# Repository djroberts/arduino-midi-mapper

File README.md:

# arduino-midi-mapper
Midi mapper using an arduino nano.

The main object is to create a device between a Gig Rig and a Digitech Whammy DT which maps program changes from the Gig Rig to the fixed patches on the DT. 

Requires the Arduino Midi Library
http://playground.arduino.cc/Main/MIDILibrary

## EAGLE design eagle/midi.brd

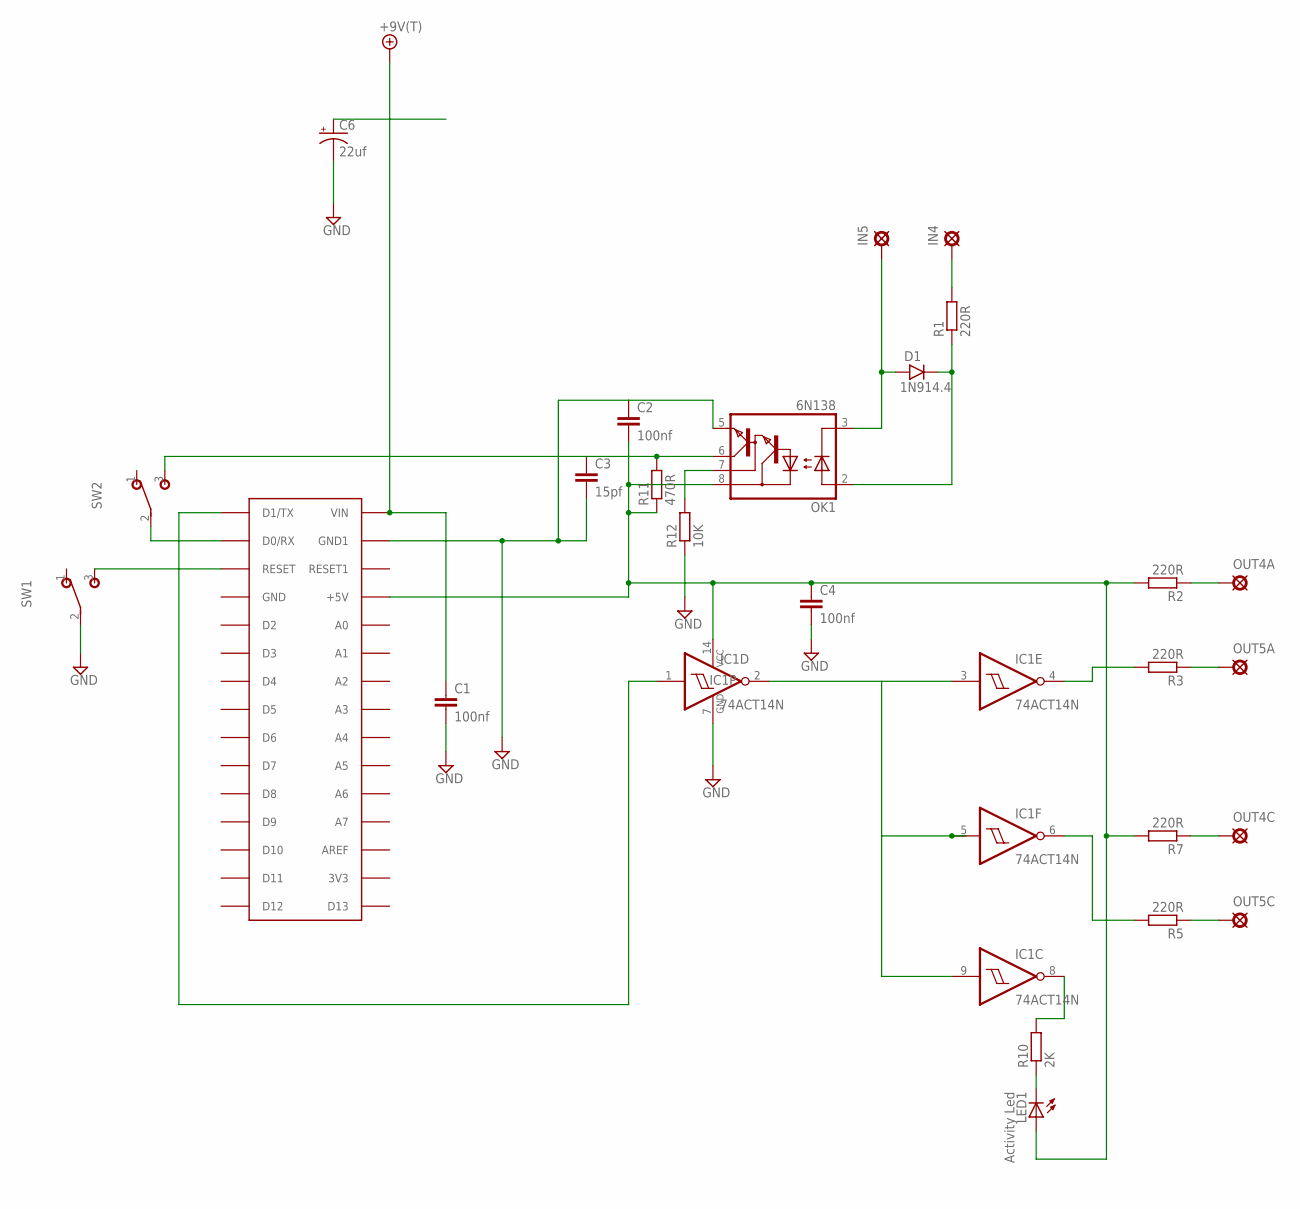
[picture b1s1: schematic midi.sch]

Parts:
+9V1: +9V(T); SQUARE
C1, C2, C4: 100nf; C5B2.5
C3: 15pf; 050X030_025
C6: 22uf; 050_020_1
D1: 1N914.4; DO35-4
IC1: 74ACT14N; DIL14
IN4, IN5: PAD8; OCTOGON
LED1: Activity Led; LED_1206
OK1: 6N138; DIL08
OUT4A, OUT4C, OUT5A, OUT5C: PAD8; OCTOGON
R1, R2, R3, R5, R7: 220R; 0204/7
R10: 2K; 0204/7
R11: 470R; 0204/7
R12: 10K; 0204/7
SW1, SW2: SPDT; M9040P
U$1: ARDUINONANO; PDIP-32

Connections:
+9V: +9V1.1, C1.1, C6.+, U$1.VIN
GND: C1.2, C2.1, C3.2, C4.2, C6.-, IC1.7 (GND), OK1.5 (GND), R12.1, SW1.2, U$1.GND1
unnamed: D1.C, OK1.2 (A), R1.1
unnamed: IN4.1, R1.2
unnamed: D1.A, IN5.1, OK1.3 (C)
unnamed: C2.2, C4.1, IC1.14 (VCC), LED1.A, OK1.8 (VCC), R2.2, R7.2, R11.1, U$1.+5V
unnamed: OK1.7 (VB), R12.2
unnamed: C3.1, OK1.6 (VO), R11.2, SW2.3 (S)
unnamed: IC1.1 (I), U$1.D1/TX
unnamed: IC1.2 (O), IC1.3 (I), IC1.5 (I), IC1.9 (I)
unnamed: OUT4A.1, R2.1
unnamed: OUT5A.1, R3.1
unnamed: OUT5C.1, R5.1
unnamed: OUT4C.1, R7.1
unnamed: IC1.4 (O), R3.2
unnamed: IC1.6 (O), R5.2
unnamed: IC1.8 (O), R10.2
unnamed: LED1.C, R10.1
unnamed: SW1.3 (S), U$1.RESET
unnamed: SW2.2, U$1.D0/RX

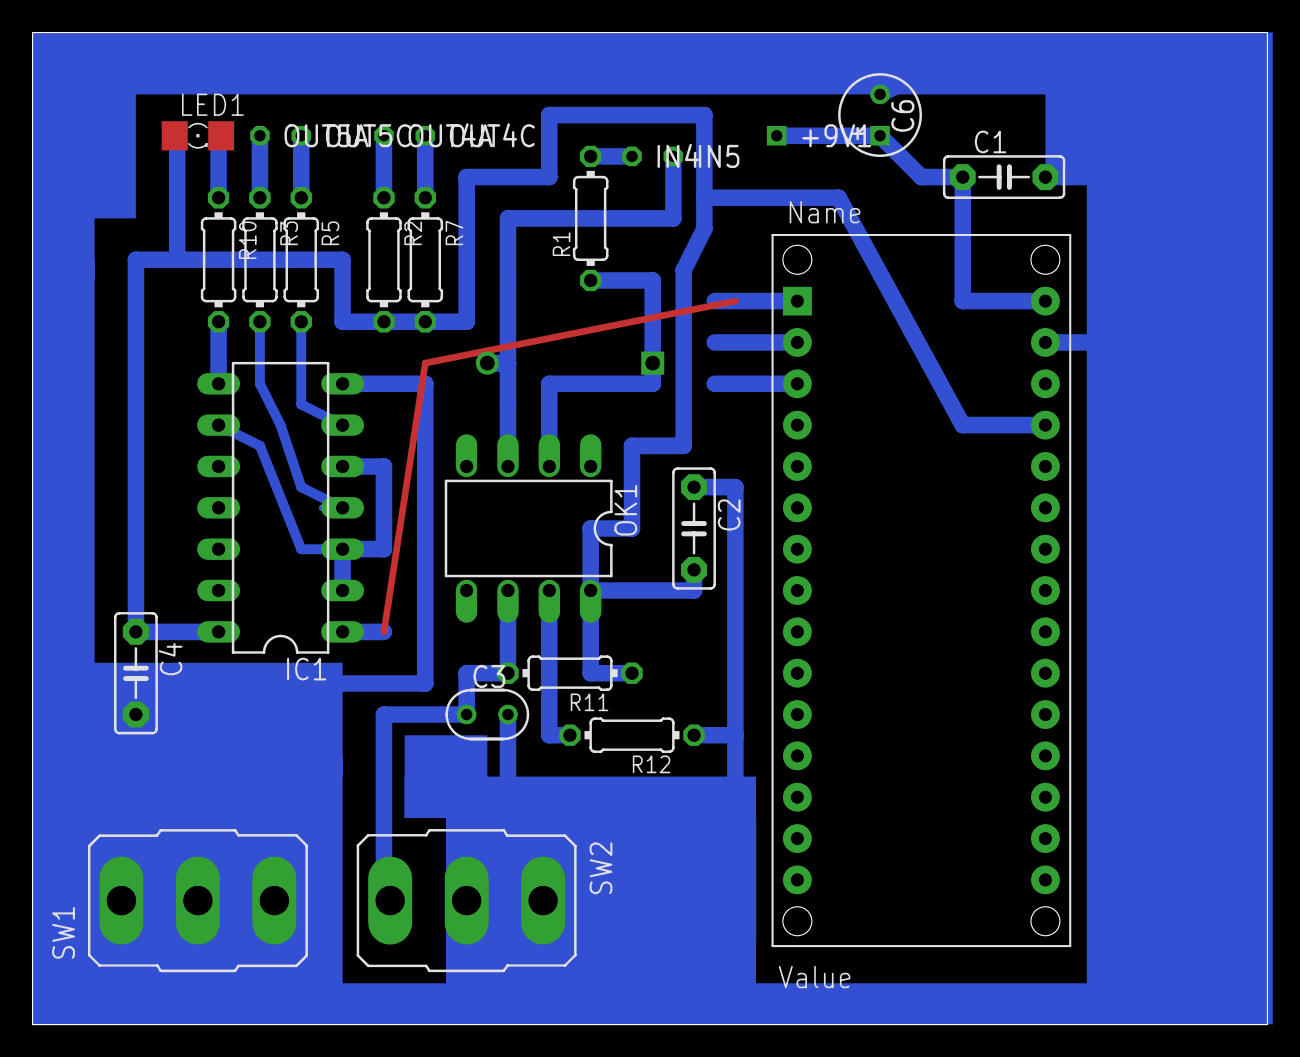
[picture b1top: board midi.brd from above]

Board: 2 copper layers, 75.9 x 61.0 mm, 27 parts (1 on the bottom side), 20 nets.

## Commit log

2016-03-02 commit test
2016-03-02 adding eagle files
2016-03-05 readme
2016-03-05 Get simple pass thru working
